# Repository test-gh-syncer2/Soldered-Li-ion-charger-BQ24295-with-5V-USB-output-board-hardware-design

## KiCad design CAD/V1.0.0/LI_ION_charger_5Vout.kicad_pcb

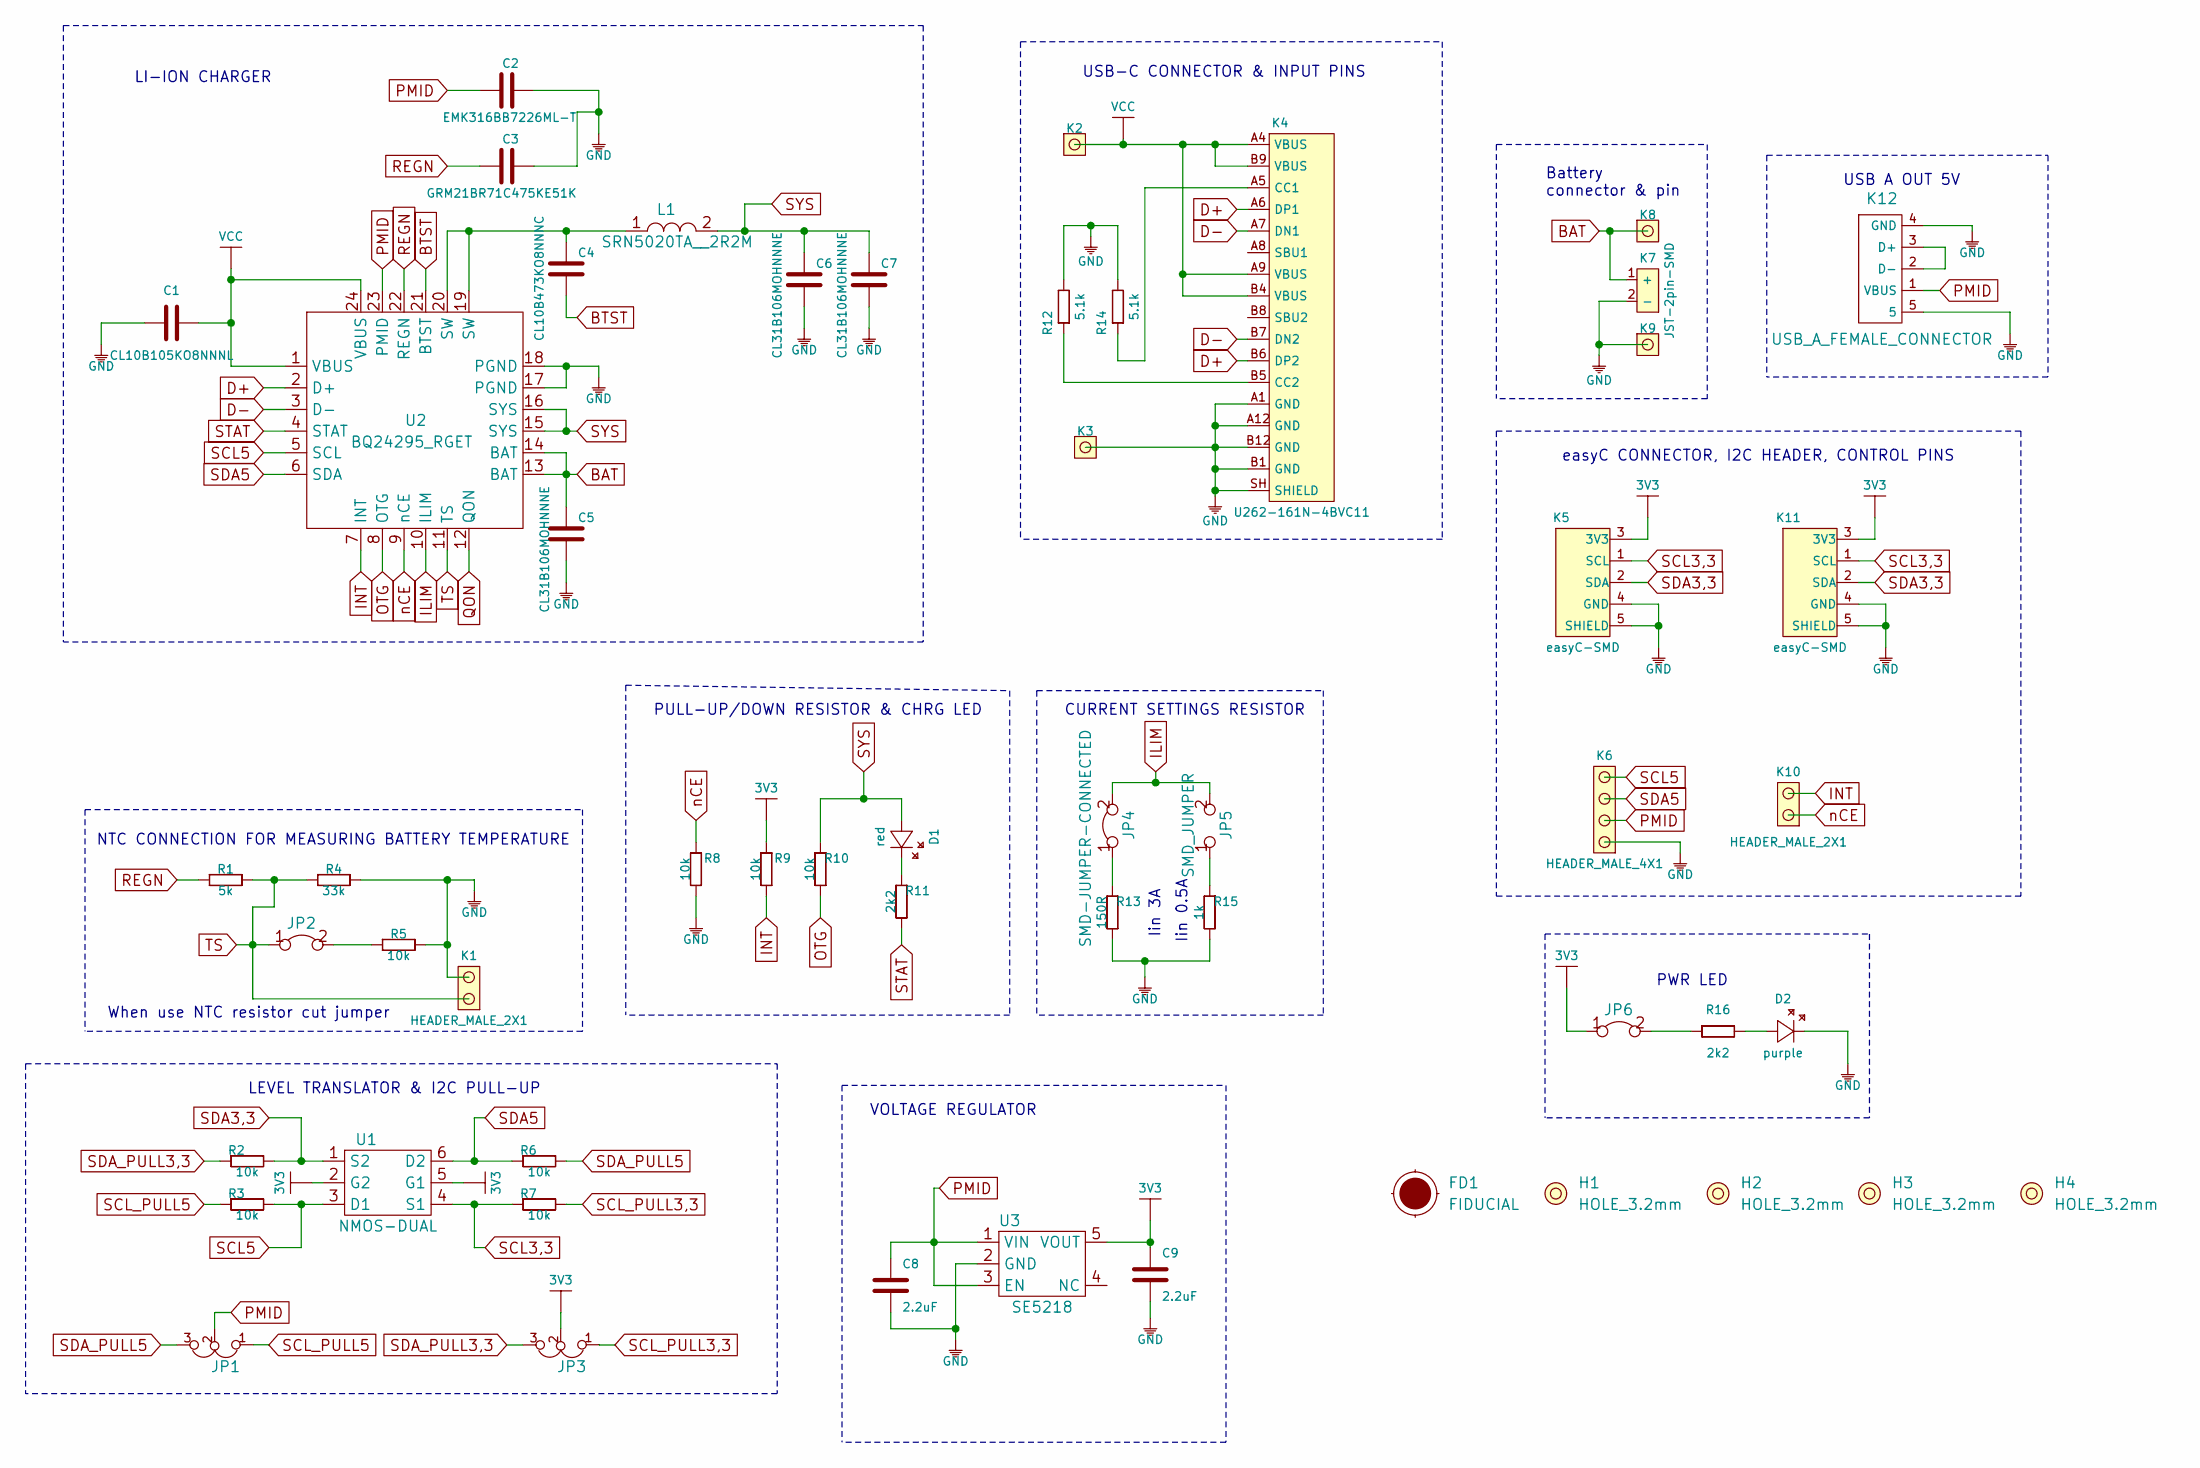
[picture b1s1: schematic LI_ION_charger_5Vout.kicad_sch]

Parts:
C1: CL10B105KO8NNNL; 0603C
C2: EMK316BB7226ML-T; 1206C
C3: GRM21BR71C475KE51K; 0805C
C4: CL10B473KO8NNNC; 0603C
C5, C6, C7: CL31B106MOHNNNE; 1206C
C8, C9: 2.2uF; 0603C
D1: red; 0402LED
D2: purple; 0402LED
FD1: FIDUCIAL; FIDUCIAL_23
H1, H2, H3, H4: HOLE_3.2mm
JP1, JP3: SMD_JUMPER_3_PAD_TRACE
JP2, JP6: SMD-JUMPER-CONNECTED_TRACE_SLODERMASK
JP4: SMD-JUMPER-CONNECTED; SMD_JUMPER_CONNECTED
JP5: SMD_JUMPER
K1, K10: HEADER_MALE_2X1
K2, K3, K8, K9: HEADER_MALE_1X1
K4: U262-161N-4BVC11
K5, K11: easyC-SMD; easyC-connector
K6: HEADER_MALE_4X1
K7: JST-2pin-SMD
K12: USB_A_FEMALE_CONNECTOR; USB_A_FEMALE_CONECTOR
L1: SRN5020TA__2R2M; SRN5020TA-2R2M
R1: 5k; 0603R
R2, R3, R5, R6, R7, R8, R9, R10: 10k; 0603R
R4: 33k; 0603R
R11, R16: 2k2; 0402R
R12, R14: 5.1k; 0603R
R13: 150R; 0603R
R15: 1k; 0603R
U1: NMOS-DUAL; SOT-363
U2: BQ24295_RGET; BQ24295RGET
U3: SE5218; SOT-23-5

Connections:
3V3: C9.2, JP3.2, JP6.1, K5.3 (3V3), K11.3 (3V3), R9.1, U1.2 (G2), U1.5 (G1), U3.5 (VOUT)
BAT: C5.2, K7.1 (+), K8.1, U2.13 (BAT), U2.14 (BAT)
BTST: C4.1, U2.21 (BTST)
D+: K4.A6 (DP1), K4.B6 (DP2), U2.2 (D+)
D-: K4.A7 (DN1), K4.B7 (DN2), U2.3 (D-)
GND: C1.1, C2.1, C3.1, C5.1, C6.1, C7.1, C8.1, C9.1, D2.2 (K), K1.2, K3.1, K4.A1 (GND), K4.A12 (GND), K4.B1 (GND), K4.B12 (GND), K4.SH (SHIELD), K5.4 (GND), K5.5 (SHIELD), K6.1, K7.2 (-), K9.1, K11.4 (GND), K11.5 (SHIELD), K12.4 (GND), K12.5, R4.2, R5.2, R8.2, R12.2, R13.2, R14.2, R15.2, U2.17 (PGND), U2.18 (PGND), U3.2 (GND)
ILIM: JP4.2, JP5.2, U2.10 (ILIM)
INT: K10.2, R9.2, U2.7 (INT)
unnamed: C4.2, L1.1, U2.19 (SW), U2.20 (SW)
unnamed: D1.2 (K), R11.1
unnamed: D2.1 (A), R16.2
unnamed: JP2.2, R5.1
unnamed: JP4.1, R13.1
unnamed: JP5.1, R15.1
unnamed: JP6.2, R16.1
unnamed: K4.A5 (CC1), R14.1
unnamed: K4.B5 (CC2), R12.1
unnamed: K12.2 (D-), K12.3 (D+)
OTG: R10.2, U2.8 (OTG)
PMID: C2.2, C8.2, JP1.2, K6.2, K12.1 (VBUS), U2.23 (PMID), U3.1 (VIN), U3.3 (EN)
QON: U2.12 (QON)
REGN: C3.2, R1.1, U2.22 (REGN)
SCL3,3: K5.1 (SCL), K11.1 (SCL), R7.1, U1.4 (S1)
SCL5: K6.4, R3.2, U1.3 (D1), U2.5 (SCL)
SCL_PULL3,3: JP3.1, R7.2
SCL_PULL5: JP1.1, R3.1
SDA3,3: K5.2 (SDA), K11.2 (SDA), R2.2, U1.1 (S2)
SDA5: K6.3, R6.1, U1.6 (D2), U2.6 (SDA)
SDA_PULL3,3: JP3.3, R2.1
SDA_PULL5: JP1.3, R6.2
STAT: R11.2, U2.4 (STAT)
SYS: C6.2, C7.2, D1.1 (A), L1.2, R10.1, U2.15 (SYS), U2.16 (SYS)
TS: JP2.1, K1.1, R1.2, R4.1, U2.11 (TS)
VCC: C1.2, K2.1, K4.A4 (VBUS), K4.A9 (VBUS), K4.B4 (VBUS), K4.B9 (VBUS), U2.1 (VBUS), U2.24 (VBUS)
nCE: K10.1, R8.1, U2.9 (nCE)

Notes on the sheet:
NTC CONNECTION FOR MEASURING BATTERY TEMPERATURE
When use NTC resistor cut jumper
LI-ION CHARGER
LEVEL TRANSLATOR & I2C PULL-UP
PULL-UP/DOWN RESISTOR & CHRG LED
VOLTAGE REGULATOR
CURRENT SETTINGS RESISTOR
Iin 3A
Iin 0.5A
USB-C CONNECTOR & INPUT PINS
Battery connector & pin
easyC CONNECTOR, I2C HEADER, CONTROL PINS
PWR LED
USB A OUT 5V

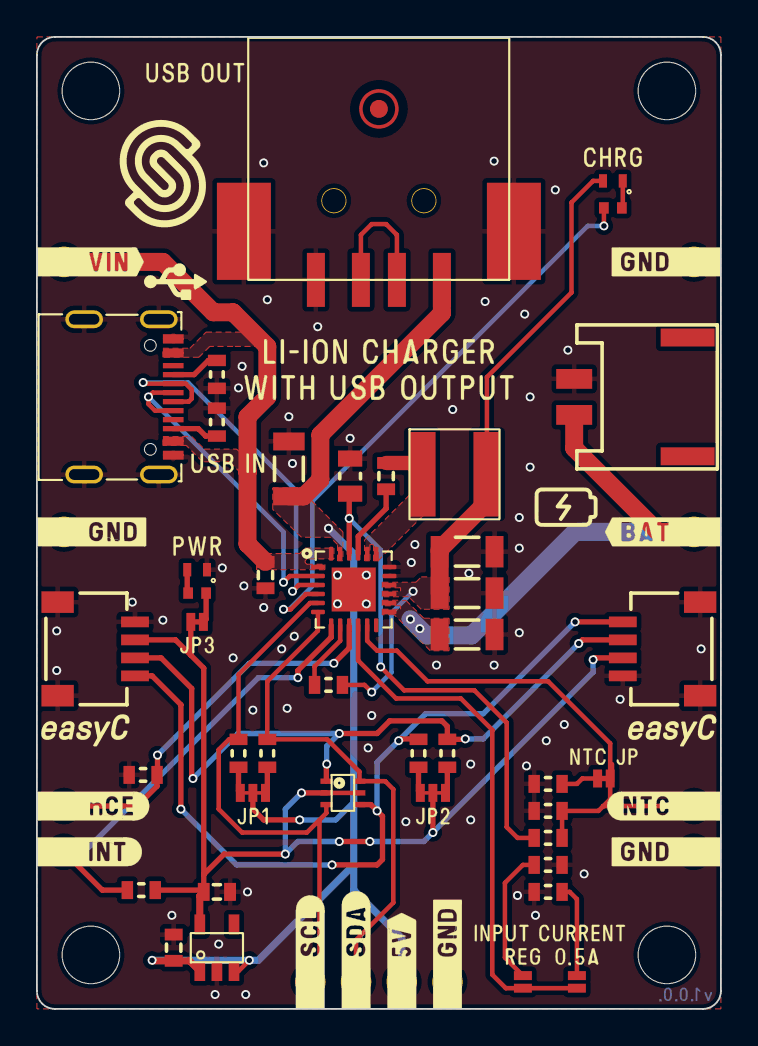
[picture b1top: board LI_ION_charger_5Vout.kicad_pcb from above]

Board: 2 copper layers, 38.0 x 54.0 mm, 55 parts (1 on the bottom side), 34 nets.

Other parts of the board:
Ref**: Val**; Version1.0.0.

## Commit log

2021-09-23 Syncing to git
2021-09-23 Updating open source files.
